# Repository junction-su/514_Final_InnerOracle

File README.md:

# 🔮 InnerOracle: Biometric Fortune Teller

## 1. Project Overview
**InnerOracle** is an interactive, tangible interface that translates physiological stress into mystical guidance. Unlike traditional fortune-telling machines that rely on random chance, InnerOracle utilizes **Galvanic Skin Response (GSR)** to measure the user's emotional arousal and provides a personalized Tarot reading through a mechanical dial and an OLED display.

## 2. Technical Complexity & System Architecture
The system is built with a **Dual-Node Architecture** using two Seeed Studio XIAO ESP32-C3 microcontrollers communicating via the **ESP-NOW** wireless protocol.

### [Sensing Node]
* **Microcontroller**: Seeed Studio XIAO ESP32-C3
* **Sensor**: Grove GSR Sensor with custom Copper Tape Electrodes
* **Logic**: Implements an **Adaptive Baseline Tracking** algorithm to detect emotional triggers beyond skin resistance fluctuations.
* **Feedback**: Provides immediate visual feedback via NeoPixel LED (Rainbow effect).

### [Display Node]
* **Microcontroller**: Seeed Studio XIAO ESP32-C3
* **Actuator**: **X27.168 Stepper Motor** (Precision Gauge Motor)
* **Display**: 0.96" I2C SSD1306 OLED
* **Logic**: Receives real-time stress data and controls the physical needle with custom homing and calibration sequences.

## 3. Data Flow
`[User's Hand] -> [GSR Sensor] -> [Sensing XIAO] --(ESP-NOW Wireless)--> [Display XIAO] -> [X27 Motor & OLED]`

## 4. Hardware Fabrication
* **Custom PCB**: Designed and soldered at GIX Prototyping Labs.
* **Enclosure**: 2-part 3D printed housing ("The Orb" and "The Dial Box").
* **Power**: Powered by 3.7V 1000mAh LiPo batteries, optimized for up to 150+ hours of typical usage.

## 5. Repository Structure
* `/Sensing_Node`: Source code for GSR data processing and ESP-NOW transmission.
* `/Display_Node`: Source code for motor control, OLED UI, and data reception.

## 6. Budget Summary
* Total Project Cost: **$66.95**
* Key Components: GSR Sensor ($32.99), 1000mAh Batteries ($16.98), XIAO ESP32C3 ($10.99).

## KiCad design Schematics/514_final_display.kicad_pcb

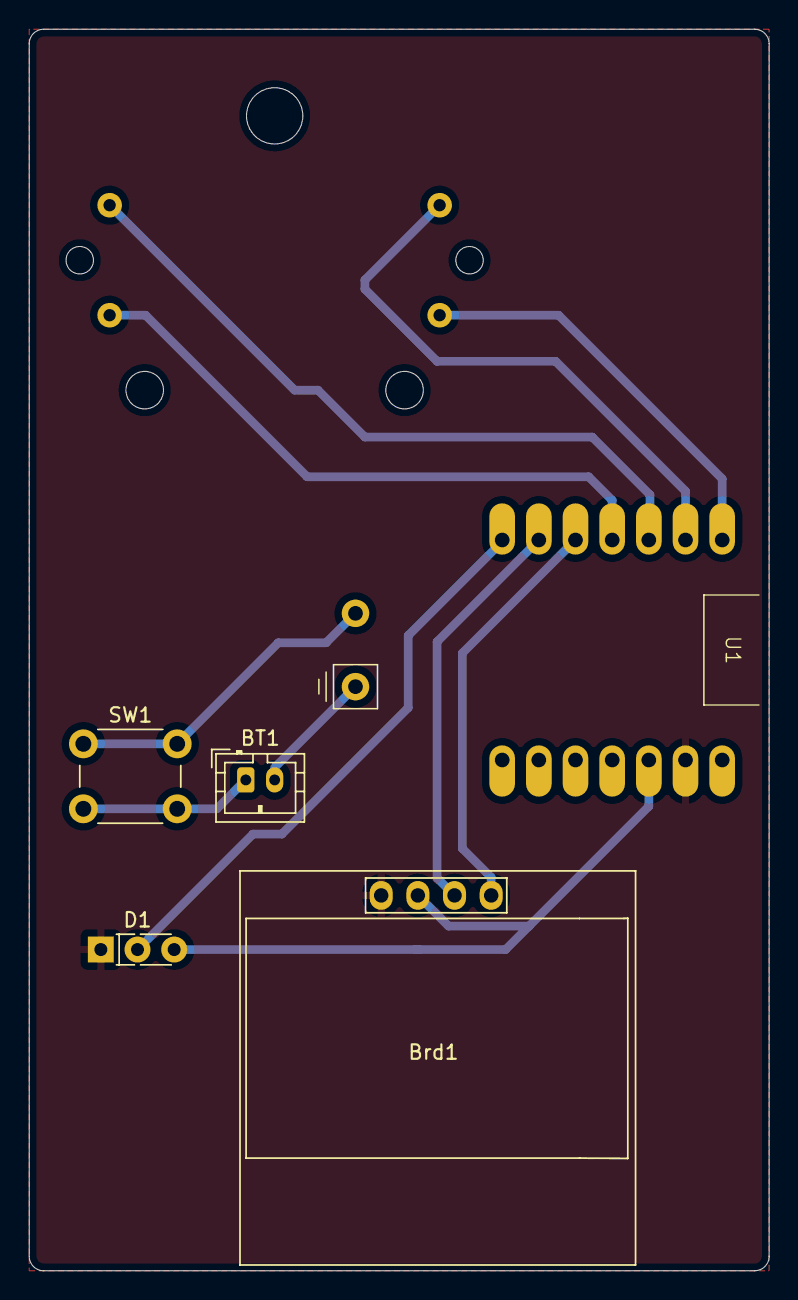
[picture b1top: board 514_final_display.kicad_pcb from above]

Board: 2 copper layers, 51.2 x 86.0 mm, 6 parts (0 on the bottom side), 12 nets.

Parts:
BT1: Battery_Cell; JST_PH_B2B-PH-K_1x02_P2.00mm_Vertical
Brd1: SSD1306; 128x64OLED
D1: NeoPixel_THT; LED_Rectangular_W5.0mm_H2.0mm-3Pins
M1: Stepper_Motor_bipolar; x27_stepper_two_holes
SW1: SW_Push; SW_PUSH_6mm
U1: ESP32-C3-XIAO; XIAO_ESP32

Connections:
3V3: Brd1.2 (VCC), D1.3 (VDD), U1.12 (3V3)
+BATT: SW1.1, U1.15 (+BATT)
-BATT: BT1.2 (-), U1.16 (-BATT)
GND: Brd1.1 (GND), D1.1 (DOUT), U1.13 (GND)
unnamed: BT1.1 (+), SW1.2
unnamed: Brd1.3 (SCL), U1.6 (GPIO6_A5_D5_SCL)
unnamed: Brd1.4 (SDA), U1.5 (GPIO4_A3_D3_SDA)
unnamed: D1.2 (GND), U1.7 (GPIO43_TX_D6)
unnamed: M1.2 (-), U1.1 (GPIO1_A0_D0)
unnamed: M1.1, U1.2 (GPIO2_A1_D1)
unnamed: M1.3, U1.3 (GPIO3_A2_D2)
unnamed: M1.4, U1.4 (GPIO4_A3_D3)

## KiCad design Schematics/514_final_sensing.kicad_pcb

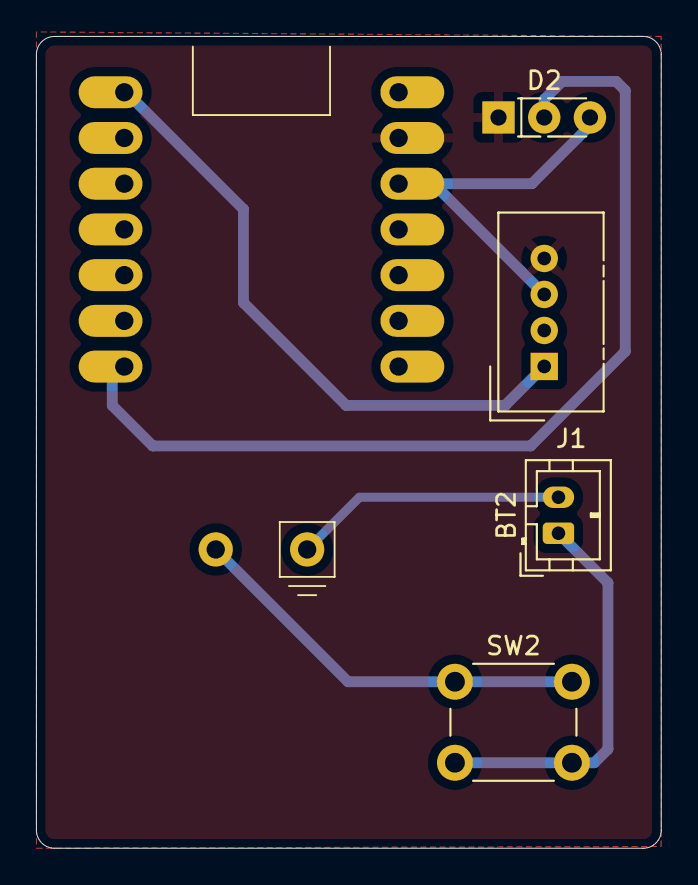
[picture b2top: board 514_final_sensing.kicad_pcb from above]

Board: 2 copper layers, 34.7 x 45.1 mm, 5 parts (0 on the bottom side), 7 nets.

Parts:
BT2: Battery_Cell; JST_PH_B2B-PH-K_1x02_P2.00mm_Vertical
D2: NeoPixel_THT; LED_Rectangular_W5.0mm_H2.0mm-3Pins
J1: SMD Grove; NS-Tech_Grove_1x04_P2mm_Vertical
SW2: SW_Push; SW_PUSH_6mm
U2: ESP32-C3-XIAO; XIAO_ESP32

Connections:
3V3_S: D2.3 (VDD), J1.3, U2.12 (3V3)
+BATT_S: SW2.1, U2.15 (+BATT)
-BATT_S: BT2.2 (-), U2.16 (-BATT)
/SIG: J1.1, U2.1 (GPIO1_A0_D0)
GND: D2.1 (DOUT), J1.4, U2.13 (GND)
unnamed: BT2.1 (+), SW2.2
unnamed: D2.2 (GND), U2.7 (GPIO43_TX_D6)

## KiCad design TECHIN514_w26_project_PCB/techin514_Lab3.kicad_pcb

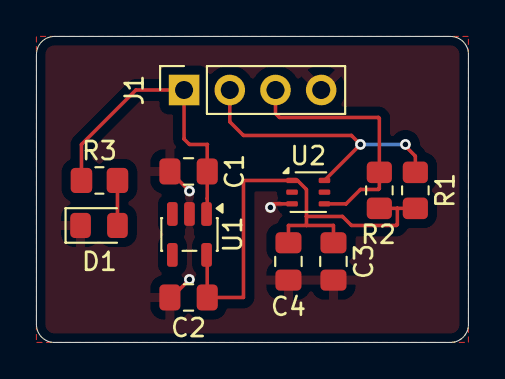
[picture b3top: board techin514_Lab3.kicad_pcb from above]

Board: 2 copper layers, 24.0 x 17.0 mm, 11 parts (0 on the bottom side), 6 nets.

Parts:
C1, C2: 1uf; C_0805_2012Metric_Pad1.18x1.45mm_HandSolder
C3: 0.1uf; C_0805_2012Metric_Pad1.18x1.45mm_HandSolder
C4: 4.7uf; C_0805_2012Metric_Pad1.18x1.45mm_HandSolder
D1: LED; LED_0805_2012Metric_Pad1.15x1.40mm_HandSolder
J1: Conn_01x04_Pin; PinSocket_1x04_P2.54mm_Vertical
R1, R2: 10k; R_0805_2012Metric_Pad1.20x1.40mm_HandSolder
R3: 1k; R_0805_2012Metric_Pad1.20x1.40mm_HandSolder
U1: MIC5376; SOT-23-5
U2: LTR390; Lite-On_LTR-303ALS-01

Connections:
+2.8V: C2.1, C3.1, C4.1, R1.2, R2.2, U1.5 (VOUT), U2.1 (VDD)
+5V: C1.1, J1.1, R3.1, U1.1 (VIN), U1.3 (EN)
/SCL: J1.3, R2.1, U2.4 (SCL)
/SDA: J1.2, R1.1, U2.6 (SDA)
GND: C1.2, C2.2, C3.2, C4.2, D1.1 (K), J1.4, U1.2 (GND), U2.3 (GND)
unnamed: D1.2 (A), R3.2

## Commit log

2026-01-20 Update README with project details
2026-01-20 Update datasheet links in datasheets.md
    Updated datasheet links for Gear Stepper Motor Driver and added ESP32-C3 datasheet.
2026-01-20 Add test.txt
2026-01-20 add idea img
2026-01-20 Change concept sketch image link in README
    Updated the concept sketch image path in the README.
2026-01-20 add png
2026-01-20 Add datasheets for Li-Po Battery, Push Button, and WS2812B
2026-01-20 Revise README for clarity and structure
    Updated the README to clarify the project components and functionality.
2026-01-20 add 2 detailed img
2026-01-20 edit
    Updated system diagram image format and removed note about sketch.
2026-01-20 add diagram
2026-01-20 add uln200,ws2812b,lipo,esp32c3,ssd1306,cx28byj48
2026-01-20 add TactileSwitch datasheet
2026-01-20 change datasheets_SourceList.md file name
2026-01-25 make a folder
2026-01-25 upload final schematics and bom
2026-01-25 Update system diagram image in README
2026-01-25 make a pcb lab folder
2026-01-25 upload pcb lab sch and bom
2026-01-29 Create d
2026-01-29 Upload Kicad files and bom
2026-02-04 Revise Gear Stepper Motor Driver Pack details
    Updated the Gear Stepper Motor Driver Pack entry with a new link and removed outdated entries.
2026-02-04 Update links for stepper motor and LED datasheets
2026-02-07 Fix link for Gear Stepper Motor Driver Pack
    Updated the link for Gear Stepper Motor Driver Pack.
2026-02-07 Update Gear Stepper Motor description in datasheet
2026-02-28 Add ESP-NOW GSR sensor data transmission
2026-03-14 Final Submission: Sensing and Display nodes for InnerOracle
2026-03-14 Revise README for InnerOracle project details
    Updated project name and enhanced descriptions for clarity. Added technical details about the sensing and display nodes, along with a budget summary.
